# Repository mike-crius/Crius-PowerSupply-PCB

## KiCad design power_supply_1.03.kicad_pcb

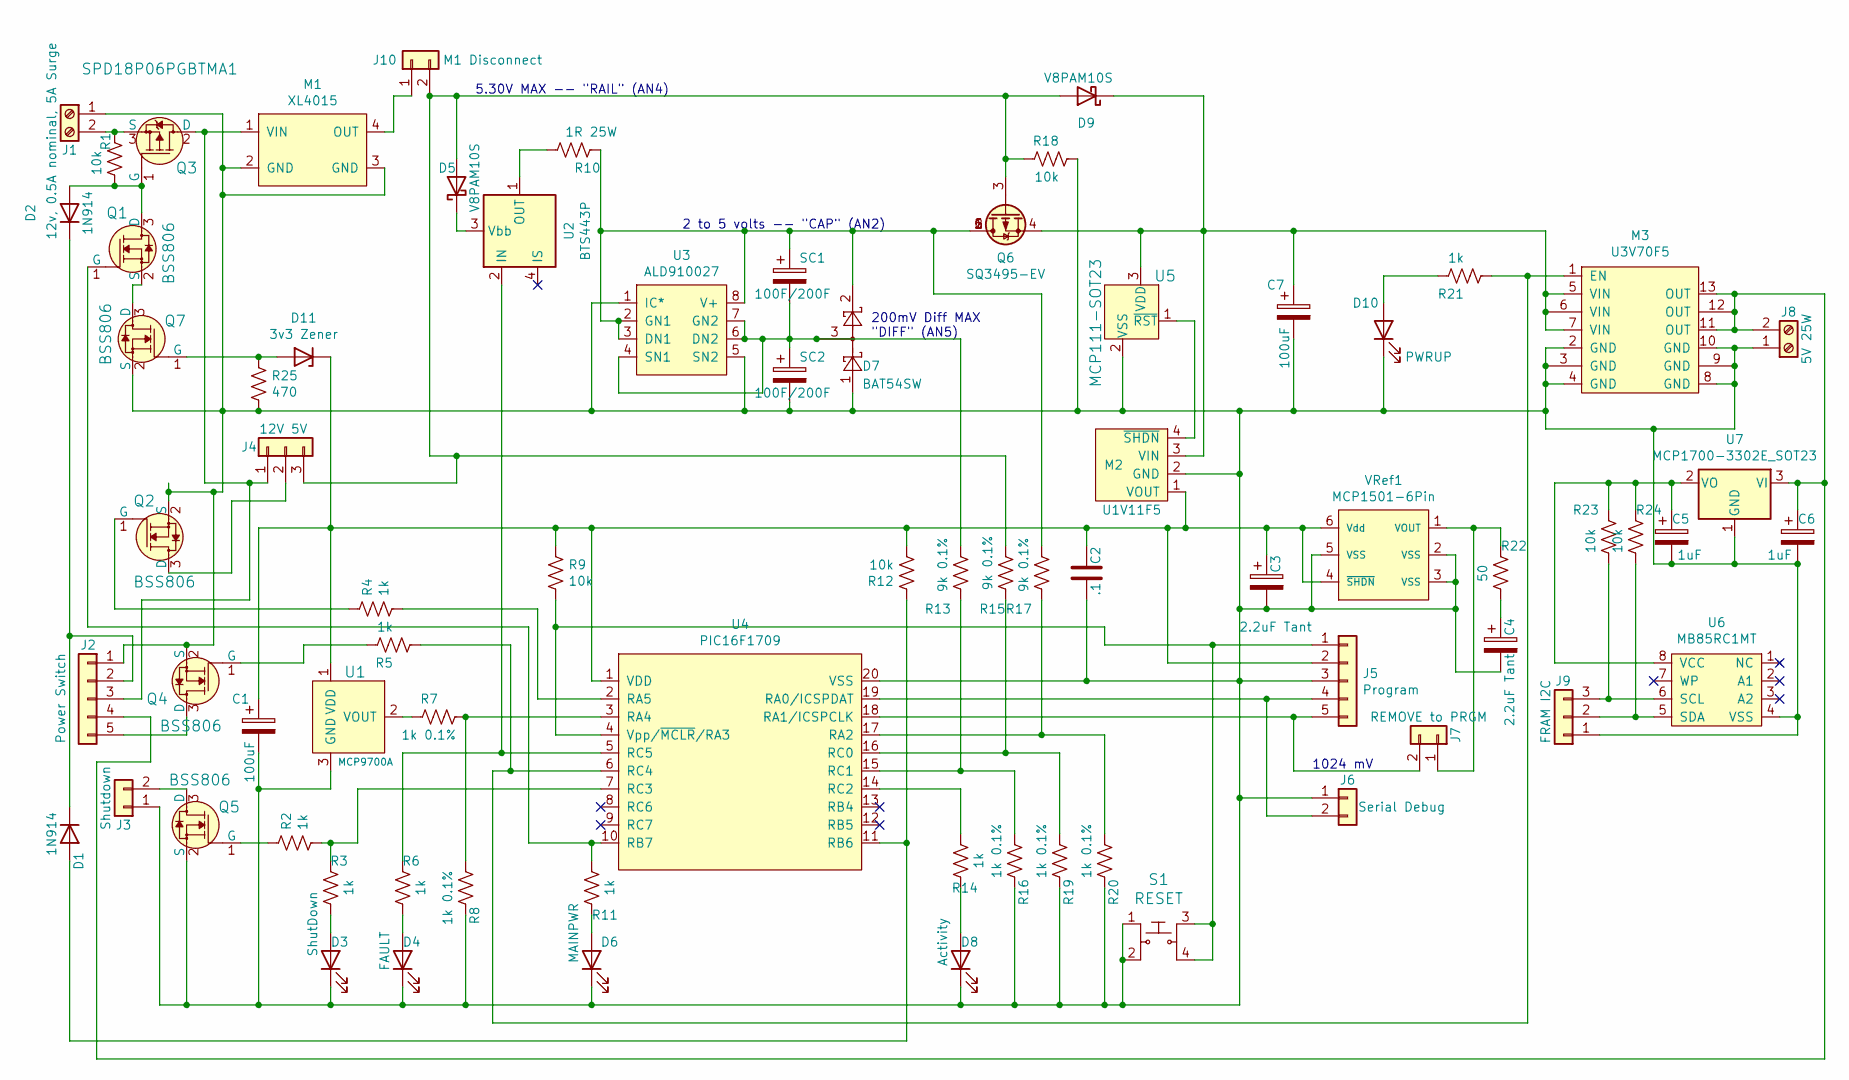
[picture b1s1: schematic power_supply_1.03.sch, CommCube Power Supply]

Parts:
C1, C7: 100uF; CP_Elec_6.3x5.2; Part# 661-EMVY160ADA101MF5
C2: .1; C_1206_3216Metric_Pad1.33x1.80mm_HandSolder; Part# 77-VJ1206Y104MXJPBC
C3, C4: 2.2uF Tant; CP_EIA-3216-18_Kemet-A; Part# 80-T491A225K010
C5, C6: 1uF; C_1206_3216Metric_Pad1.33x1.80mm_HandSolder; Part# 80-C1206C105K3RAUTO
D1, D2: 1N914; D_SOD-123F; Part# 821-1N914BWRHG
D3: ShutDown; D_1206_3216Metric_Castellated; Part# 645-598-8240-107F
D4: FAULT; D_1206_3216Metric_Castellated; Part# 645-598-8220-107F
D5, D9: V8PAM10S; DO-221BC; Part# 78-V8PAM10SHM3/H
D6: MAINPWR; D_1206_3216Metric_Castellated; Part# 645-598-8270-107F
D7: BAT54SW; SOT-323_SC-70; Part# 771-BAT54SWF
D8: Activity; D_1206_3216Metric_Castellated; Part# 645-598-8291-107F
D10: PWRUP; D_1206_3216Metric_Castellated; Part# 645-598-8270-107F
D11: 3v3 Zener; D_SOD-123F; Part# 771-NZH3V3A-115
J1: 12v, 0.5A nominal, 5A Surge; Screw_Terminal_2Pin
J2: Power Switch; JST_XH_B5B-XH-A_1x05_P2.50mm_Vertical
J3: Shutdown; PinHeader_1x02_P2.54mm_Vertical
J4: 12V 5V; JST_XH_B3B-XH-A_1x03_P2.50mm_Vertical
J5: Program; PinHeader_1x05_P2.54mm_Vertical
J6: Serial Debug; PinHeader_1x02_P2.54mm_Vertical
J7: REMOVE to PRGM; PinHeader_1x02_P2.54mm_Vertical
J8: 5V 25W; Screw_Terminal_2Pin
J9: FRAM I2C; JST_XH_B3B-XH-A_1x03_P2.50mm_Vertical
J10: M1 Disconnect; PinHeader_1x02_P2.54mm_Vertical
M1: XL4015
M2: U1V11F5; U1V11Fx; Part# 2562
M3: U3V70F5; Part# 2891
Q1, Q2, Q4, Q7: BSS806; SOT-23-3; MPN BSS138; Digi-Key_PN BSS138CT-ND
Q3: SPD18P06PGBTMA1; TO-252-3_TabPin2; MPN IRF9540NPBF; Digi-Key_PN IRF9540NPBF-ND
Q5: BSS806; SOT-23-3; Part# 726-BSS806NEH6327XTS
Q6: SQ3495-EV; SOT-23-6; Part# 78-SQ3495EV-T1_GE3
R1, R9, R12, R18, R23, R24: 10k; R_1206_3216Metric; Part# 603-RT1206FRD0710KL
R2, R3, R4, R5, R6, R11, R14, R21: 1k; R_1206_3216Metric; Part# 603-RT1206FRD071KL
R7, R8, R16, R19, R20: 1k 0.1%; R_1206_3216Metric; Part# 603-RT1206BRD071KL
R10: 1R 25W; SolderWire-0.5sqmm_1x02_P4.6mm_D0.9mm_OD2.1mm; Part# 71-RH0251R000FE02
R13, R15, R17: 9k 0.1%; R_1206_3216Metric; Part# 603-RT1206BRD079KL
R22: 50; R_1206_3216Metric; Part# 660-RN732BTTD50R0B25
R25: 470; R_1206_3216Metric; Part# 603-RT1206FRE07470RL
S1: RESET; Panasonic 6x6mm EVQ-7Q201W; MPN 1825910-6; Digi-Key_PN 450-1650-ND
SC1, SC2: 100F/200F; SCC-22-30mm; Part# 581-SCCW45B107SSB / 581-SCCW45B207SSB
U1: MCP9700A; SOT-23-3; Part# 579-MCP9700AT-E/TT
U2: BTS443P; TO-252-4; Part# 726-BTS443P
U3: ALD910027; SOIC-8_3.9x4.9mm_P1.27mm; Part# 585-ALD910027SAL
U4: PIC16F1709; SOIC-20W_7.5x12.8mm_P1.27mm; Part# 579-PIC16F1709T-I/SO
U5: MCP111-SOT23; SOT-23-3; MPN MCP130T-300I/TT; Digi-Key_PN MCP130T-300I/TTCT-ND
U6: MB85RC1MT; SOIC-8_3.9x4.9mm_P1.27mm; Part# 249-85C1MTPNFGJNERE1
U7: MCP1700-3302E_SOT23; SOT-23; Part# 579-MCP1700T3302E/TT
VRef1: MCP1501-6Pin; SOT-23-6; Part# 579-MCP1501T-10E/CHY

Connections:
unnamed: C1.1, C2.2, C3.1, D11.1 (K), J5.2, M2.1 (VOUT), R9.2, R12.1, U1.1 (VDD), U4.1 (VDD), VRef1.4 (~SHDN), VRef1.6 (Vdd)
unnamed: C1.2, C2.1, C3.2, C4.2, C5.2, C6.2, C7.2, D3.1 (K), D4.1 (K), D6.1 (K), D7.1, D8.1 (K), D10.1 (K), J1.1, J2.1, J3.1, J5.3, J6.1, J8.1, J9.1, M1.2 (GND), M1.3 (GND), M2.2 (GND), M3.2 (GND), M3.3 (GND), M3.4 (GND), M3.8 (GND), M3.9 (GND), M3.10 (GND), Q2.2 (S), Q4.2 (S), Q5.2 (S), Q7.2 (S), R8.2, R16.1, R18.1, R19.1, R20.1, R25.1, S1.1, S1.2, SC2.1, U1.3 (GND), U3.1 (IC*), U3.5 (SN2), U4.20 (VSS), U5.2 (VSS), U6.4 (VSS), U7.1 (GND), VRef1.2 (VSS), VRef1.3 (VSS), VRef1.5 (VSS)
unnamed: C4.1, R22.2
unnamed: C5.1, R23.1, R24.1, U6.8 (VCC), U7.2 (VO)
unnamed: C6.1, J2.4, J8.2, M3.11 (OUT), M3.12 (OUT), M3.13 (OUT), U7.3 (VI)
unnamed: C7.1, D9.1 (K), M2.3 (VIN), M3.5 (VIN), M3.6 (VIN), M3.7 (VIN), Q6.4 (S), U5.3 (VDD)
unnamed: D1.1 (K), D2.1 (K), J2.2
unnamed: D1.2 (A), R12.2, U4.11 (RB6)
unnamed: D2.2 (A), Q1.3 (D), Q3.1 (G), R1.2
unnamed: D3.2 (A), R3.2
unnamed: D4.2 (A), R6.2
unnamed: D5.1 (K), U2.3 (Vbb)
unnamed: D5.2 (A), D9.2 (A), J4.3, J10.2, Q6.3 (G), R15.2, R18.2
unnamed: D6.2 (A), R11.2
unnamed: D7.2, Q6.1 (D), Q6.2 (D), Q6.5 (D), Q6.6 (D), R10.2, R17.1, SC1.2, U3.2 (GN1), U3.3 (DN1), U3.8 (V+)
unnamed: D7.3, R13.1, SC1.1, SC2.2, U3.4 (SN1), U3.6 (DN2), U3.7 (GN2)
unnamed: D8.2 (A), R14.2
unnamed: D10.2 (A), R21.2
unnamed: D11.2 (A), Q7.1 (G), R25.2
unnamed: J1.2, Q3.3 (S), R1.1
unnamed: J2.3, J4.1, M1.1 (VIN), Q3.2 (D)
unnamed: J2.5, Q4.3 (D)
unnamed: J3.2, Q5.3 (D)
unnamed: J4.2, Q2.3 (D)
unnamed: J5.1, R9.1, S1.3, S1.4, U4.4 (Vpp/~MCLR~/RA3)
unnamed: J5.4, J6.2, U4.19 (RA0/ICSPDAT)
unnamed: J5.5, J7.2, U4.18 (RA1/ICSPCLK)
unnamed: J7.1, R22.1, VRef1.1 (VOUT)
unnamed: J9.2, R24.2, U6.5 (SDA)
unnamed: J9.3, R23.2, U6.6 (SCL)
unnamed: J10.1, M1.4 (OUT)
unnamed: M2.4 (~SHDN), U5.1 (~RST)
unnamed: M3.1 (EN), R5.1, R21.1, U4.6 (RC4)
unnamed: Q1.1 (G), R11.1, U4.10 (RB7)
unnamed: Q1.2 (S), Q7.3 (D)
unnamed: Q2.1 (G), R4.2
unnamed: Q4.1 (G), R5.2
unnamed: Q5.1 (G), R2.2
unnamed: R2.1, R3.1, U4.7 (RC3)
unnamed: R4.1, U4.2 (RA5)
unnamed: R6.1, U2.2 (IN), U4.5 (RC5)
unnamed: R7.1, R8.1, U4.3 (RA4)
unnamed: R7.2, U1.2 (VOUT)
unnamed: R10.1, U2.1 (OUT), U2.5 (OUT)
unnamed: R13.2, R16.2, U4.15 (RC1)
unnamed: R14.1, U4.14 (RC2)
unnamed: R15.1, R19.2, U4.16 (RC0)
unnamed: R17.2, R20.2, U4.17 (RA2)

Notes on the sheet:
2 to 5 volts -- "CAP" (AN2)
1024 mV
5.30V MAX -- "RAIL" (AN4)
200mV Diff MAX "DIFF" (AN5)

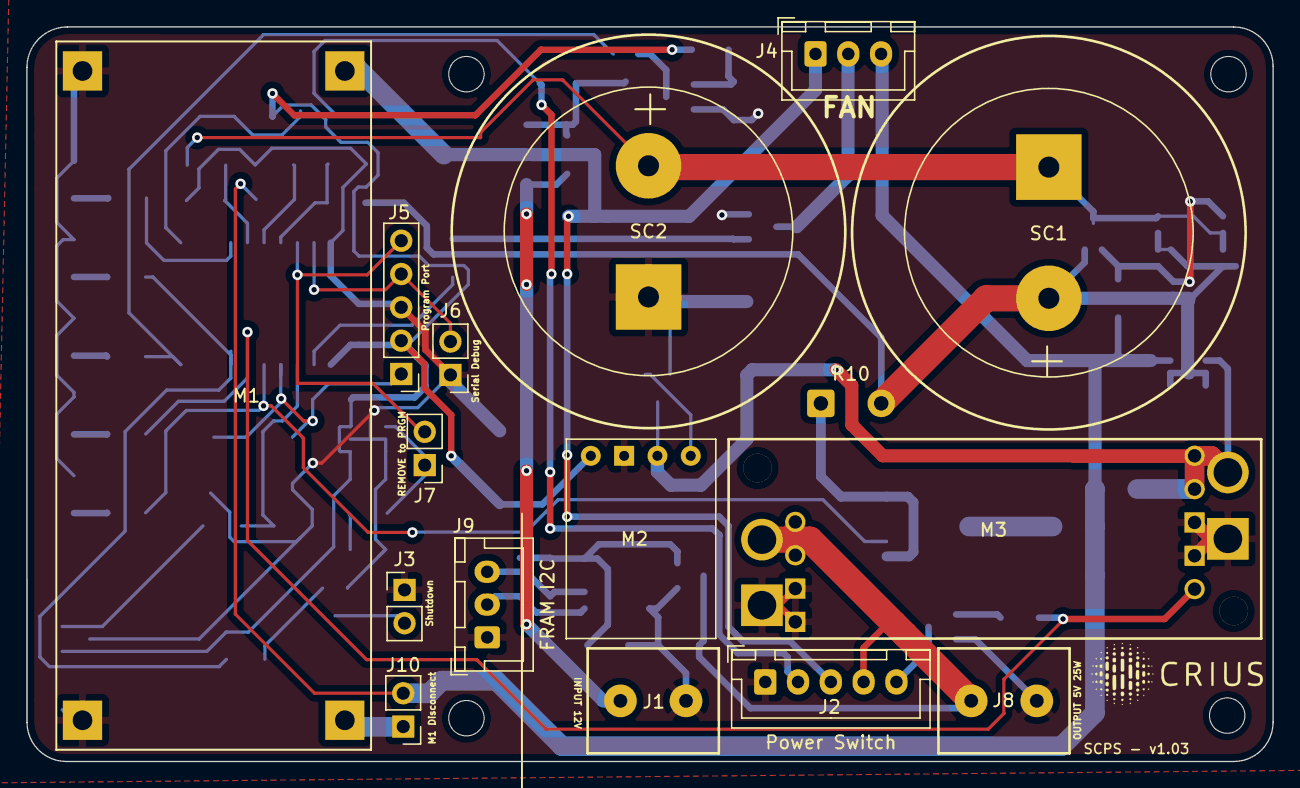
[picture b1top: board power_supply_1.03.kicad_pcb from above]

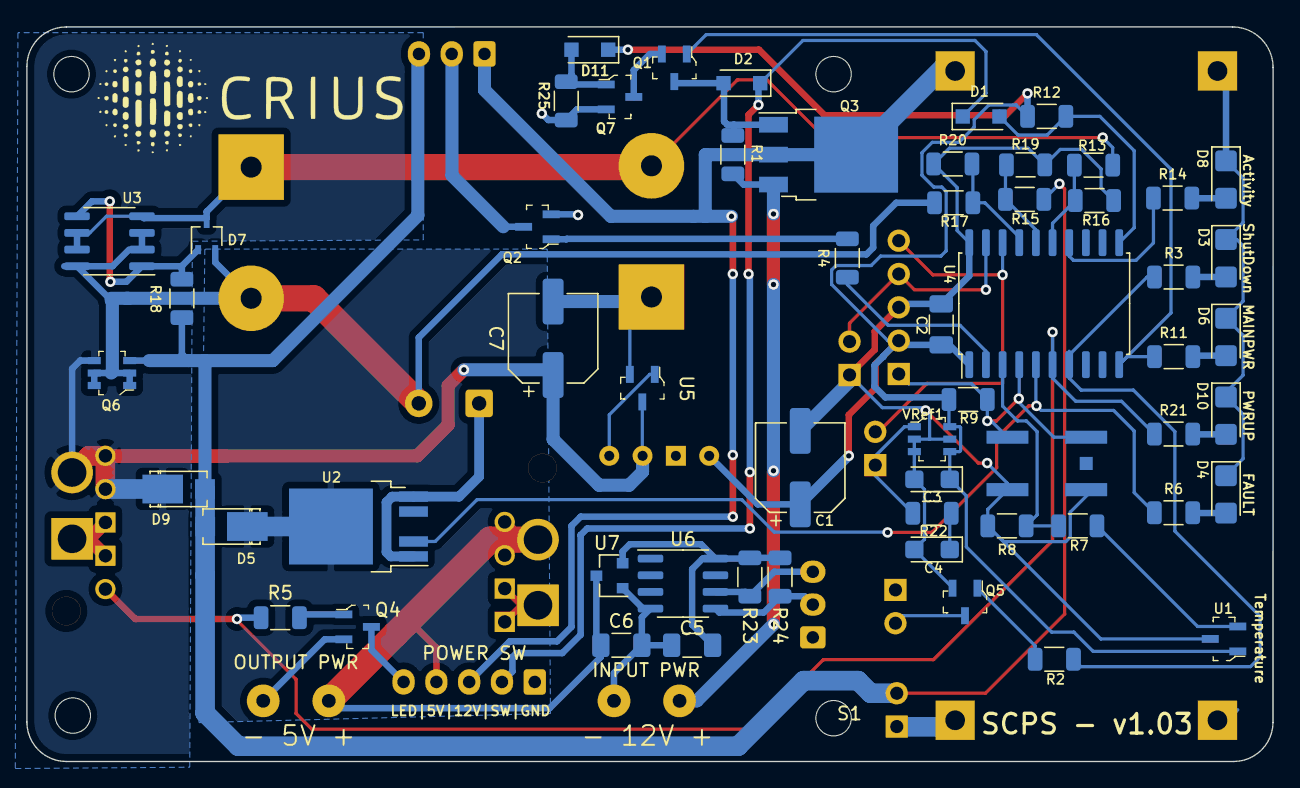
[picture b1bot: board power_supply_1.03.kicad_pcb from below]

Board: 2 copper layers, 95.0 x 56.0 mm, 74 parts (58 on the bottom side), 48 nets.

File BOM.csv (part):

Reference, Quantity, Value, Footprint, Datasheet, Part#, Vendor, Category, DK_Datasheet_Link, DK_Detail_Page, Description, Digi-Key_PN, Family, MPN, Manufacturer, Status
C1 C7 ,2,"100uF","Capacitor_SMD:CP_Elec_6.3x5.2","https://www.mouser.com/datasheet/2/420/MVYRA_e-2509074.pdf","661-EMVY160ADA101MF5","Mouser","","","","","","","","",""
C2 ,1,".1","Capacitor_SMD:C_1206_3216Metric_Pad1.33x1.80mm_HandSolder","https://www.mouser.com/datasheet/2/427/VISH_S_A0011539493_1-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","77-VJ1206Y104MXJPBC","Mouser","","","","","","","","",""
C3 C4 ,2,"2.2uF Tant","Capacitor_Tantalum_SMD:CP_EIA-3216-18_Kemet-A","https://www.mouser.com/datasheet/2/212/1/KEM_T2005_T491-1093550.pdf","80-T491A225K010","Mouser","","","","","","","","",""
C5 C6 ,2,"1uF","Capacitor_SMD:C_1206_3216Metric_Pad1.33x1.80mm_HandSolder","https://www.mouser.com/datasheet/2/212/KEM_C1023_X7R_AUTO_SM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","80-C1206C105K3RAUTO","Mouser","","","","","","","","",""
D10 ,1,"PWRUP","Diode_SMD:D_1206_3216Metric_Castellated","https://www.mouser.com/datasheet/2/109/Dialight_CBI_data_598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","645-598-8270-107F","Mouser","","","","","","","","",""
D11 ,1,"D_Zener","Diode_SMD:D_SOD-123F","https://www.mouser.com/datasheet/2/916/NZH_SER-1320207.pdf","771-NZH3V3A-115","Mouser","","","","","","","","",""
D1 D2 ,2,"1N914","Diode_SMD:D_SOD-123F","https://www.mouser.com/datasheet/2/395/1N4148W_SERIES_K1804-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","821-1N914BWRHG","Mouser","","","","","","","","",""
D3 ,1,"ShutDown","Diode_SMD:D_1206_3216Metric_Castellated","https://www.mouser.com/datasheet/2/109/Dialight_CBI_data_598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","645-598-8240-107F","Mouser","","","","","","","","",""
D4 ,1,"FAULT","Diode_SMD:D_1206_3216Metric_Castellated","https://www.mouser.com/datasheet/2/109/Dialight_CBI_data_598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","645-598-8220-107F","Mouser","","","","","","","","",""
D6 ,1,"MAINPWR","Diode_SMD:D_1206_3216Metric_Castellated","https://www.mouser.com/datasheet/2/109/Dialight_CBI_data_598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","645-598-8270-107F","Mouser","","","","","","","","",""
D7 ,1,"BAT54SW","Package_TO_SOT_SMD:SOT-323_SC-70","https://www.mouser.com/datasheet/2/916/BAT54W_SER-1598288.pdf","771-BAT54SWF","Mouser","","","","","","","","",""
D8 ,1,"Activity","Diode_SMD:D_1206_3216Metric_Castellated","https://www.mouser.com/datasheet/2/109/Dialight_CBI_data_598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","645-598-8291-107F","Mouser","","","","","","","","",""
D5 D9 ,2,"V8PAM10S","Footprint_Library:DO-221BC","https://www.vishay.com/doc?87013","78-V8PAM10SHM3/H","Mouser","","","","","","","","",""
J1 ,1,"12v, 0.5A nominal, 5A Surge","Connectors:Screw_Terminal_2Pin","~","https://www.amazon.com/Pieces-Pinch-Mount-Terminal-Connector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","Amazon","","","","","","","","",""
J2 ,1,"Power Switch","Connector_JST:JST_XH_B5B-XH-A_1x05_P2.50mm_Vertical","~","https://www.amazon.com/Header-Lystaii-Pin-Connector-Electron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","Amazon","","","","","","","","",""
J3 ,1,"Shutdown","Connector_PinHeader_2.54mm:PinHeader_1x02_P2.54mm_Vertical","~","https://www.amazon.com/Header-Lystaii-Pin-Connector-Electron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","Amazon","","","","","","","","",""
J4 ,1,"12V  5V","Connector_PinHeader_2.54mm:PinHeader_1x03_P2.54mm_Vertical","~","https://www.amazon.com/Header-Lystaii-Pin-Connector-Electron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","Amazon","","","","","","","","",""
J5 ,1,"Program","Connector_PinHeader_2.54mm:PinHeader_1x05_P2.54mm_Vertical","~","https://www.amazon.com/Header-Lystaii-Pin-Connector-Electron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","Amazon","","","","","","","","",""
J6 ,1,"Serial Debug","Connector_PinHeader_2.54mm:PinHeader_1x02_P2.54mm_Vertical","~","https://www.amazon.com/Header-Lystaii-Pin-Connector-Electron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","Amazon","","","","","","","","",""
J7 ,1,"REMOVE to PRGM","Connector_PinHeader_2.54mm:PinHeader_1x02_P2.54mm_Vertical","~","https://www.amazon.com/Header-Lystaii-Pin-Connector-Electron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","Amazon","","","","","","","","",""
J8 ,1,"5V 25W","Connectors:Screw_Terminal_2Pin","~","https://www.amazon.com/Pieces-Pinch-Mount-Terminal-Connector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","Amazon","","","","","","","","",""
J9 ,1,"FRAM I2C","Connector_JST:JST_XH_B3B-XH-A_1x03_P2.50mm_Vertical","~","https://www.amazon.com/Header-Lystaii-Pin-Connector-Electron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","Amazon","","","","","","","","",""
M1 ,1,"XL4015","Footprint_Library:XL4015","","https://www.amazon.com/Adjustable-Converter-1-25-36v-Efficie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","Amazon","","","","","","","","",""
M2 ,1,"U1V11F5","Pololu:U1V11Fx","https://www.pololu.com/product/2562","2562","Pololu","","","","","","","","",""
M3 ,1,"U3V70F5","Pololu:U3V70F5","https://www.pololu.com/product/2891","2891","Pololu","","","","","","","","",""
Q1 Q2 Q4 Q5 Q7 ,5,"BSS806","digikey-footprints:SOT-23-3","https://www.mouser.com/datasheet/2/196/Infineon-BSS806NE-DS-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","726-BSS806NEH6327XTS","Mouser","Discrete Semiconductor Products","https://www.onsemi.com/pub/Collateral/BSS138-D.PDF","/product-detail/en/on-semiconductor/BSS138/BSS138CT-ND/244294","MOSFET N-CH 50V 220MA SOT-23","BSS138CT-ND","Transistors - FETs, MOSFETs - Single","BSS138","ON Semiconductor","Active"
Q3 ,1,"SPD18P06PGBTMA1","Package_TO_SOT_SMD:TO-252-3_TabPin2","https://www.mouser.com/datasheet/2/196/Infineon-SPD18P06P-DS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","726-SPD18P06P","Mouser","Discrete Semiconductor Products","https://www.infineon.com/dgdl/irf9540npbf.pdf?fileId=5546d46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","/product-detail/en/infineon-technologies/IRF9540NPBF/IRF9540NPBF-ND/812088","MOSFET P-CH 100V 23A TO-220AB","IRF9540NPBF-ND","Transistors - FETs, MOSFETs - Single","IRF9540NPBF","Infineon Technologies","Active"
Q6 ,1,"SQ3495-EV","digikey-footprints:SOT-23-6","https://www.mouser.com/datasheet/2/427/sq3495ev-1868467.pdf","78-SQ3495EV-T1_GE3","Mouser","","","","","","","","",""
R10 ,1,"1R 25W","Connector_Wire:SolderWire-0.5sqmm_1x02_P4.6mm_D0.9mm_OD2.1mm","https://www.mouser.com/datasheet/2/427/VISH_S_A0003599165_1-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","71-RH0251R000FE02","Mouser","","","","","","","","",""
R2 R3 R4 R5 R6 R11 R14 R21 ,8,"1k","Resistor_SMD:R_1206_3216Metric","https://www.mouser.com/datasheet/2/447/PYu_RT_1_to_0_01_RoHS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","603-RT1206FRD071KL","Mouser","","","","","","","","",""
R13 R15 R17 ,3,"9k 0.1%","Resistor_SMD:R_1206_3216Metric","https://www.mouser.com/datasheet/2/447/PYu_RT_1_to_0_01_RoHS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","603-RT1206BRD079KL","Mouser","","","","","","","","",""
R7 R8 R16 R19 R20 ,5,"1k 0.1%","Resistor_SMD:R_1206_3216Metric","https://www.mouser.com/datasheet/2/447/PYu_RT_1_to_0_01_RoHS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","603-RT1206BRD071KL","Mouser","","","","","","","","",""
R22 ,1,"50","Resistor_SMD:R_1206_3216Metric","https://www.mouser.com/datasheet/2/219/KOA_Speer_RN73__1_-18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","660-RN732BTTD50R0B25","Mouser","","","","","","","","",""
R25 ,1,"470","Resistor_SMD:R_1206_3216Metric","https://www.mouser.com/datasheet/2/447/PYu_RT_1_to_0_01_RoHS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","603-RT1206FRE07470RL","Mouser","","","","","","","","",""
R1 R9 R12 R18 R23 R24 ,6,"10k","Resistor_SMD:R_1206_3216Metric","https://www.mouser.com/datasheet/2/447/PYu_RT_1_to_0_01_RoHS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","603-RT1206FRD0710KL","Mouser","","","","","","","","",""
S1 ,1,"RESET","digikey-footprints:Switch_Tactile_SMD_6x6mm","https://www.mouser.com/datasheet/2/315/sw_lt_eng_6s_th-1289042.pdf","667-EVQ-7Q201W","Mouser","Switches","https://www.te.com/commerce/DocumentDelivery/DDEController?A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","/product-detail/en/te-connectivity-alcoswitch-switches/1825910-6/450-1650-ND/1632536","SWITCH TACTILE SPST-NO 0.05A 24V","450-1650-ND","Tactile Switches","1825910-6","TE Connectivity ALCOSWITCH Switches","Active"
SC1 SC2 ,2,"100F/200F","SuperCaps:SCC-22-30mm","https://www.mouser.com/datasheet/2/40/AVX_SCC-1920423.pdf","581-SCCW45B107SSB / 581-SCCW45B207SSB","Mouser","","","","","","","","",""
U1 ,1,"MCP9700A","digikey-footprints:SOT-23-3","https://www.mouser.com/datasheet/2/268/20001942G-1820450.pdf","579-MCP9700AT-E/TT","Mouser","","","","","","","","",""
U2 ,1,"BTS443P","Package_TO_SOT_SMD:TO-252-4","https://www.mouser.com/datasheet/2/196/Infineon-BTS443P-DS-v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","726-BTS443P","Mouser","","","","","","","","",""
U3 ,1,"ALD910027","Package_SO:SOIC-8_3.9x4.9mm_P1.27mm","https://www.mouser.com/datasheet/2/8/ALD810027-464310.pdf","585-ALD910027SAL","Mouser","","","","","","","","",""
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
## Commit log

2021-09-26 Initial v0.31
2021-10-18 Version 0.35 includes updates for new parts and field updates for PCB
2021-10-23 Version 0.36 circuit part changes, completed initial parts information and BOM
2021-11-07 Version 1.0 includes fixes/changes and FRAM support
2021-11-10 Version 1.01 - Includes fixes, footprint validation, gerbers, screenshots, documentation
2021-11-11 Version 1.02 adds M1 disconnect for initial adjustment of M1
2021-11-21 Version 1.03 fixes M1, J4, SW footprints. R1 schematic error fixed. Heat sink copper area for U2, D5, D9
2022-01-09 LiPo Version 0.1 Initial schematic for LiPo version
